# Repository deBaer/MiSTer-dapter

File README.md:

# MiSTer'dapter
A VGA and audio jack to RGB SCART converter with RCA sync or composite output for the MiSTer FPGA

    Copyright (C) 2022 Simon Kowalewski

    This program is free software; you can redistribute it and/or modify
    it under the terms of the GNU General Public License as published by
    the Free Software Foundation; either version 2 of the License, or
    (at your option) any later version.

    This program is distributed in the hope that it will be useful,
    but WITHOUT ANY WARRANTY; without even the implied warranty of
    MERCHANTABILITY or FITNESS FOR A PARTICULAR PURPOSE.  See the
    GNU General Public License for more details.

    You should have received a copy of the GNU General Public License along
    with this program; if not, write to the Free Software Foundation, Inc.,
    51 Franklin Street, Fifth Floor, Boston, MA 02110-1301 USA.

## Video demonstration
[YouTube](https://youtu.be/DpnR34e562k) (Spoken languague is German, English subtitles are available)
	
## Build yourself
You'll need the [board](board) manufactured on 1.6 mm substrate. Also, you'll need a fitting SCART, VGA, RCA and mini phone jack. (I'll add links later.) You'll also need a 470 ohm resistor for attenuating the sync signal to SCART-safe levels and, optionally but recommended, a capacitor and inductance for the luma trap. I use 33 uH and 68 pF. If you don't use C1 and L1, bridge C1 with a resistor leg.

Optionally, 3D-print the [case](case). If you can multi-color print, print case.stl and print.stl together in different colors. If you cannot, don't print print.stl. If you want to use the case, populate the jumpers on the back side of the PCB (the side without silkscreen print).

## Buy from me
I don't have a web shop right now, so just send a mail to deBaer@gmail.com and tell me how many kits you want (15 €/kit), your preferred jumper color (black, white, blue, red, green and yellow available), if I should solder and test them for you (+10 €/kit), if you want cases (+10 €/case) and your post address (postage is 6€ flat for Germany for registered mail, I'll calculate the International postage on demand). I'll send you a confirmation with the expected delivery date, the final price and payment information, most likely Paypal. If you cannot or don't want to use Paypal, also indicate that in your email. Use a subject header containing "[daptor]" so I'll see the mail.

## Buy from someone else
If you offer to sell MiSTer'dapter kits, I'll list you here. Non-EU sellers are especially welcome, as I don't like customs forms. But please, attribute me and link back to this page.

## Usage
Connect the MiSTer'daptor to your MiSTer with a normal VGA cable.

Note: For the Guncon 2 or any other lightguns to work, the video has to go directly from the core to the CRT. No `vga_scaler`, no `scandoubler`! Also, no plasma, LCD, OLED! It may work with `direct_video` over the HDMI port, but that depends on both the device as well as the settings.

### RGB SCART
Connect the MiSTer'daptor to your TV with a RGB-capable SCART cable (not all are). For audio, connect the MiSTer'daptor with a normal TRS mini jack cable to the MiSTer. Optionally, connect Guncon 2 or other controllers that need sync to the RCA jack. Use these .ini settings:

```
forced_scandoubler=0
ypbpr=0 
composite_sync=1
vga_scaler=0
```

### Composite
Connect the MiSTer'daptor RCA plug to a composite input (normally yellow) on the TV. Connect the MiSTer audio out directly to the TV. You need to use [Y/C-capable cores](https://github.com/MikeS11/MiSTerFPGA_YC_Encoder) and switch to Y/C video mode in the core config dialog. Use these .ini settings:

```
forced_scandoubler=0
ypbpr=0 
composite_sync=1
vga_scaler=0
vga_sog=1
```

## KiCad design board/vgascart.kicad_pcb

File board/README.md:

# MiSTer'dapter board
A VGA and audio jack to RGB SCART converter with RCA sync or composite output for the MiSTer FPGA

    Copyright (C) 2022 Simon Kowalewski

    This program is free software; you can redistribute it and/or modify
    it under the terms of the GNU General Public License as published by
    the Free Software Foundation; either version 2 of the License, or
    (at your option) any later version.

    This program is distributed in the hope that it will be useful,
    but WITHOUT ANY WARRANTY; without even the implied warranty of
    MERCHANTABILITY or FITNESS FOR A PARTICULAR PURPOSE.  See the
    GNU General Public License for more details.

    You should have received a copy of the GNU General Public License along
    with this program; if not, write to the Free Software Foundation, Inc.,
    51 Franklin Street, Fifth Floor, Boston, MA 02110-1301 USA.

This board was created in KiCAD 6. Source files as well as ready-for-production (I use JLCPCB) files are in this directory. For more information, see the [top directory](https://github.com/deBaer/MiSTer-dapter).

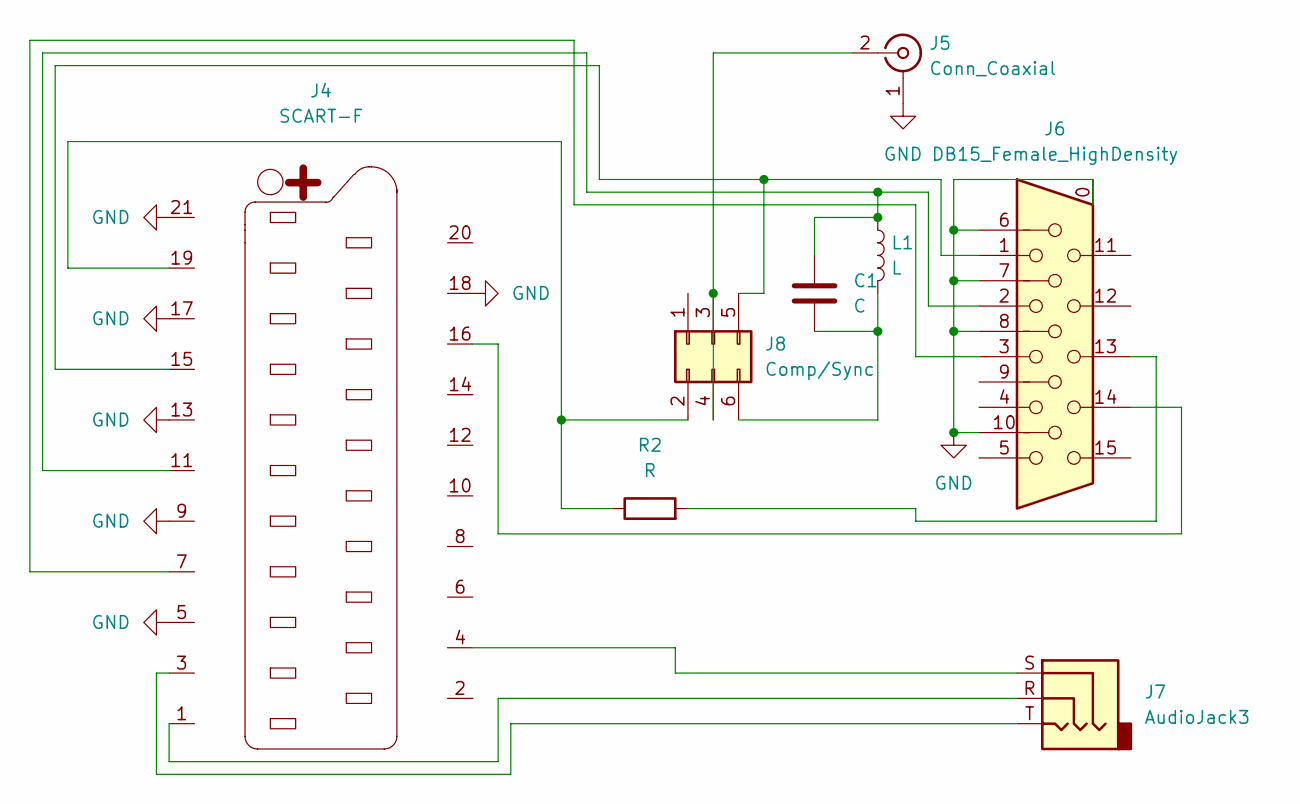
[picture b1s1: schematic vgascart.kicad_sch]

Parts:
C1: C; C_Disc_D6.0mm_W2.5mm_P5.00mm
J4: SCART-F; SCART.kicad_mod
J5: Conn_Coaxial; CBP C160
J6: DB15_Female_HighDensity; DSUB-15-HD_Female_Horizontal_P2.29x1.98mm_EdgePinOffset8.35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
J7: AudioJack3; Jack_3.5mm_Ledino_KB3SPRS_Horizontal
J8: Comp/Sync; PinHeader_2x03_P2.54mm_Vertical
L1: L; L_Axial_L6.6mm_D2.7mm_P10.16mm_Horizontal_Vishay_IM-2
R2: R; R_Axial_DIN0207_L6.3mm_D2.5mm_P7.62mm_Horizontal

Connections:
GND: J4.5, J4.9, J4.13, J4.17, J4.18, J4.21, J5.1 (Ext), J6.0, J6.6, J6.7, J6.8, J6.10
unnamed: C1.2, J8.6, L1.2
unnamed: J4.1, J7.R
unnamed: J4.3, J7.T
unnamed: J4.4, J7.S
unnamed: J4.7, J6.3
unnamed: C1.1, J4.11, J6.2, L1.1
unnamed: J4.15, J6.1, J8.5
unnamed: J4.16, J6.14
unnamed: J5.2 (In), J8.3, J8.4
unnamed: J6.13, R2.2
unnamed: J4.19, J8.2, R2.1

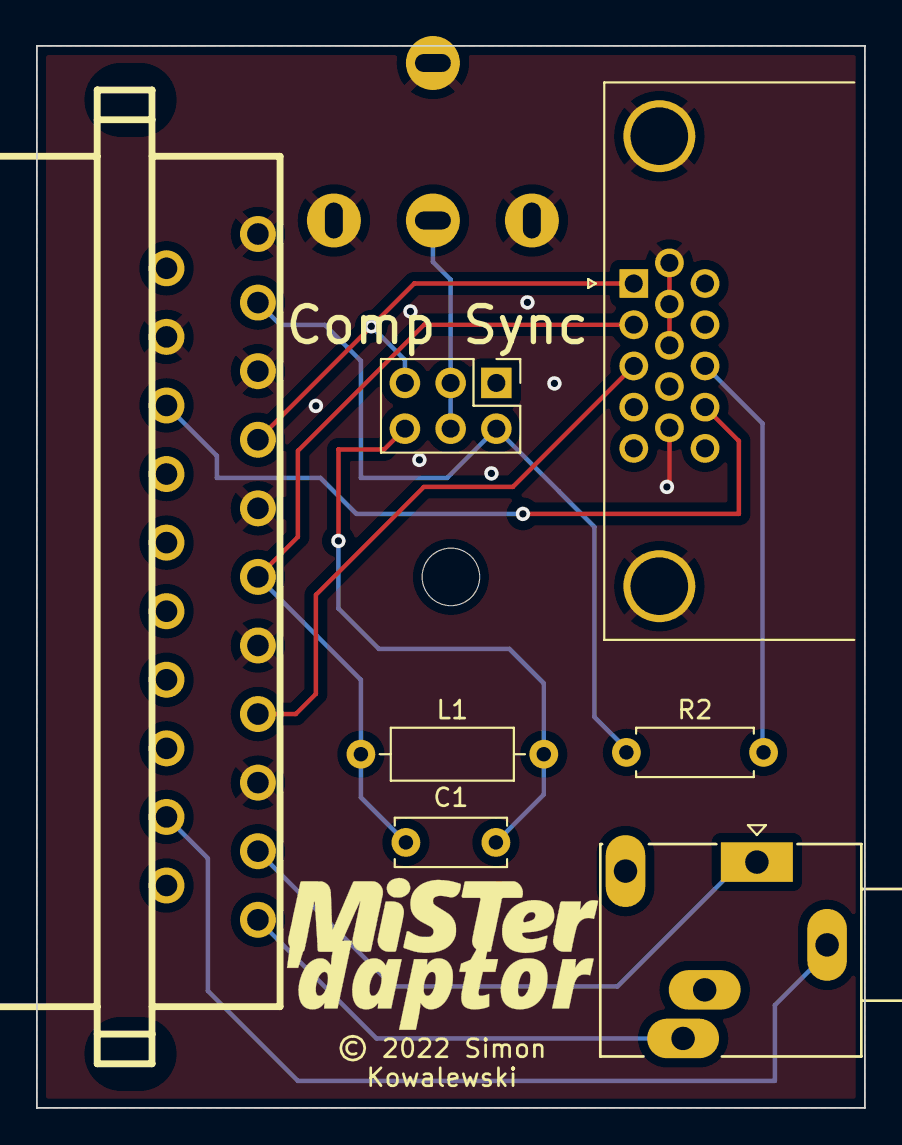
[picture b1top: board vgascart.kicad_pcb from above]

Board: 2 copper layers, 46.0 x 59.0 mm, 8 parts (0 on the bottom side), 12 nets.

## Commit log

2022-08-16 Initial commit
    Initial commit
2022-08-17 Board cleanup, README

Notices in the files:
board/vgascart.kicad_pcb:
© 2022 Simon
